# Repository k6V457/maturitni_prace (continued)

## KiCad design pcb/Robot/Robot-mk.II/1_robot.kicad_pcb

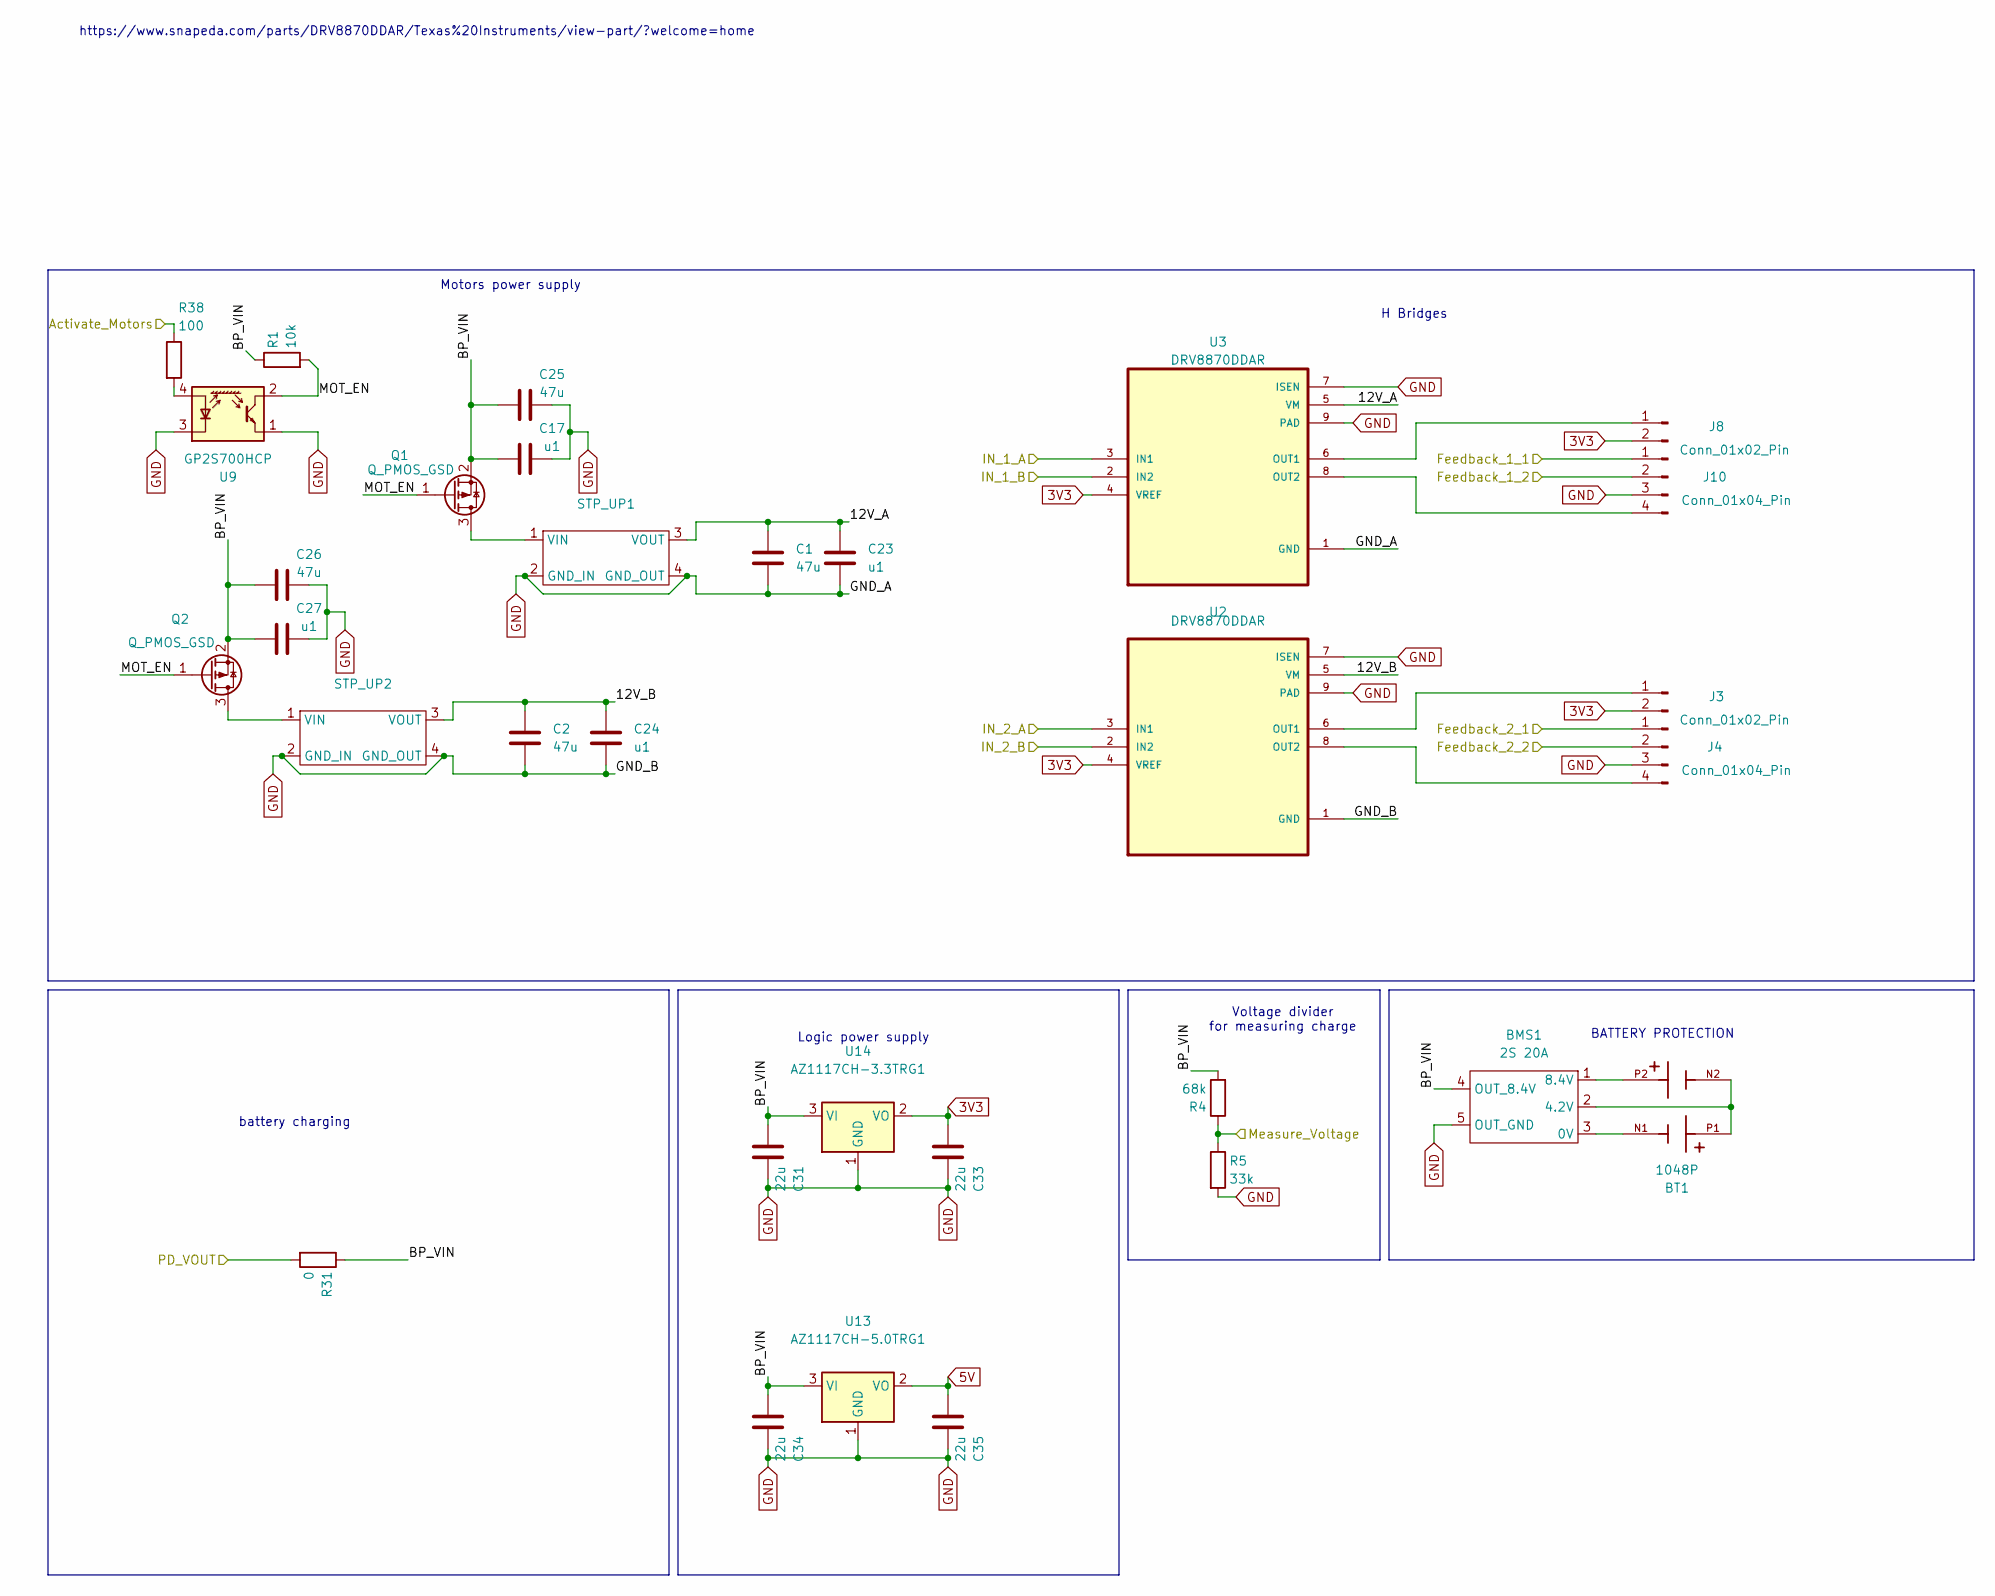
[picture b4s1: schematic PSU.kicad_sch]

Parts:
BMS1: 2S 20A; BMS
BT1: 1048P; BAT_1048P; PARTREV A
C1, C2, C25, C26: 47u; C_0805_2012Metric_Pad1.18x1.45mm_HandSolder
C17, C23, C24, C27: u1; C_0805_2012Metric_Pad1.18x1.45mm_HandSolder
C31, C33, C34, C35: 22u; C_0805_2012Metric_Pad1.18x1.45mm_HandSolder
J3, J8: Conn_01x02_Pin; JST_EH_B2B-EH-A_1x02_P2.50mm_Vertical
J4, J10: Conn_01x04_Pin; JST_EH_B4B-EH-A_1x04_P2.50mm_Vertical
Q1, Q2: Q_PMOS_GSD; SOT-23
R1: 10k; R_0805_2012Metric_Pad1.20x1.40mm_HandSolder
R4: 68k; R_0805_2012Metric_Pad1.20x1.40mm_HandSolder
R5: 33k; R_0805_2012Metric_Pad1.20x1.40mm_HandSolder
R31: 0; R_0805_2012Metric_Pad1.20x1.40mm_HandSolder
R38: 100; R_0805_2012Metric_Pad1.20x1.40mm_HandSolder
STP_UP1, STP_UP2: STP_UP
U2, U3: DRV8870DDAR; VREG_LM5017MR_NOPB
U9: GP2S700HCP; SSOP-4_4.4x2.6mm_P1.27mm
U13: AZ1117CH-5.0TRG1; SOT-223-3_TabPin2
U14: AZ1117CH-3.3TRG1; SOT-223-3_TabPin2

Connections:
3V3: C33.2, J3.2, J8.2, U2.4 (VREF), U3.4 (VREF), U14.2 (VO); also elsewhere on the board
5V: C35.2, U13.2 (VO)
/ESP32/IO1: R4.1, R5.1; also elsewhere on the board
/ESP32/IO4: J4.2; also elsewhere on the board
/ESP32/IO5: J4.1; also elsewhere on the board
/ESP32/IO6: U2.3 (IN1); also elsewhere on the board
/ESP32/IO7: U2.2 (IN2); also elsewhere on the board
/ESP32/IO14: R38.1; also elsewhere on the board
/ESP32/IO15: J10.2; also elsewhere on the board
/ESP32/IO16: J10.1; also elsewhere on the board
/ESP32/IO17: U3.3 (IN1); also elsewhere on the board
/ESP32/IO18: U3.2 (IN2); also elsewhere on the board
/Input/PD_VOUT: R31.2; also elsewhere on the board
/PSU/12V_A: C1.1, C23.1, STP_UP1.3 (VOUT), U3.5 (VM)
/PSU/12V_B: C2.1, C24.1, STP_UP2.3 (VOUT), U2.5 (VM)
/PSU/BP_VIN: BMS1.4 (OUT_8.4V), C17.2, C25.2, C26.2, C27.2, C31.2, C34.2, Q1.2 (S), Q2.2 (S), R1.1, R4.2, R31.1, U13.3 (VI), U14.3 (VI)
/PSU/MOT_EN: Q1.1 (G), Q2.1 (G), R1.2, U9.2
GND: BMS1.5 (OUT_GND), C1.2, C2.2, C17.1, C23.2, C24.2, C25.1, C26.1, C27.1, C31.1, C33.1, C34.1, C35.1, J4.3, J10.3, R5.2, STP_UP1.2 (GND_IN), STP_UP1.4 (GND_OUT), STP_UP2.2 (GND_IN), STP_UP2.4 (GND_OUT), U2.1 (GND), U2.7 (ISEN), U2.9 (PAD), U3.1 (GND), U3.7 (ISEN), U3.9 (PAD), U9.1, U9.3 (K), U13.1 (GND), U14.1 (GND); also elsewhere on the board
unnamed: BMS1.3 (0V), BT1.N1
unnamed: BMS1.2 (4.2V), BT1.N2, BT1.P1
unnamed: BMS1.1 (8.4V), BT1.P2
unnamed: J3.1, U2.6 (OUT1)
unnamed: J4.4, U2.8 (OUT2)
unnamed: J8.1, U3.6 (OUT1)
unnamed: J10.4, U3.8 (OUT2)
unnamed: Q1.3 (D), STP_UP1.1 (VIN)
unnamed: Q2.3 (D), STP_UP2.1 (VIN)
unnamed: R38.2, U9.4 (A)

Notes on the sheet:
battery charging
BATTERY PROTECTION
Logic power supply
H Bridges
Motors power supply
Voltage divider for measuring charge
https://www.snapeda.com/parts/DRV8870DDAR/Texas%20Instruments/view-part/?welcome=home

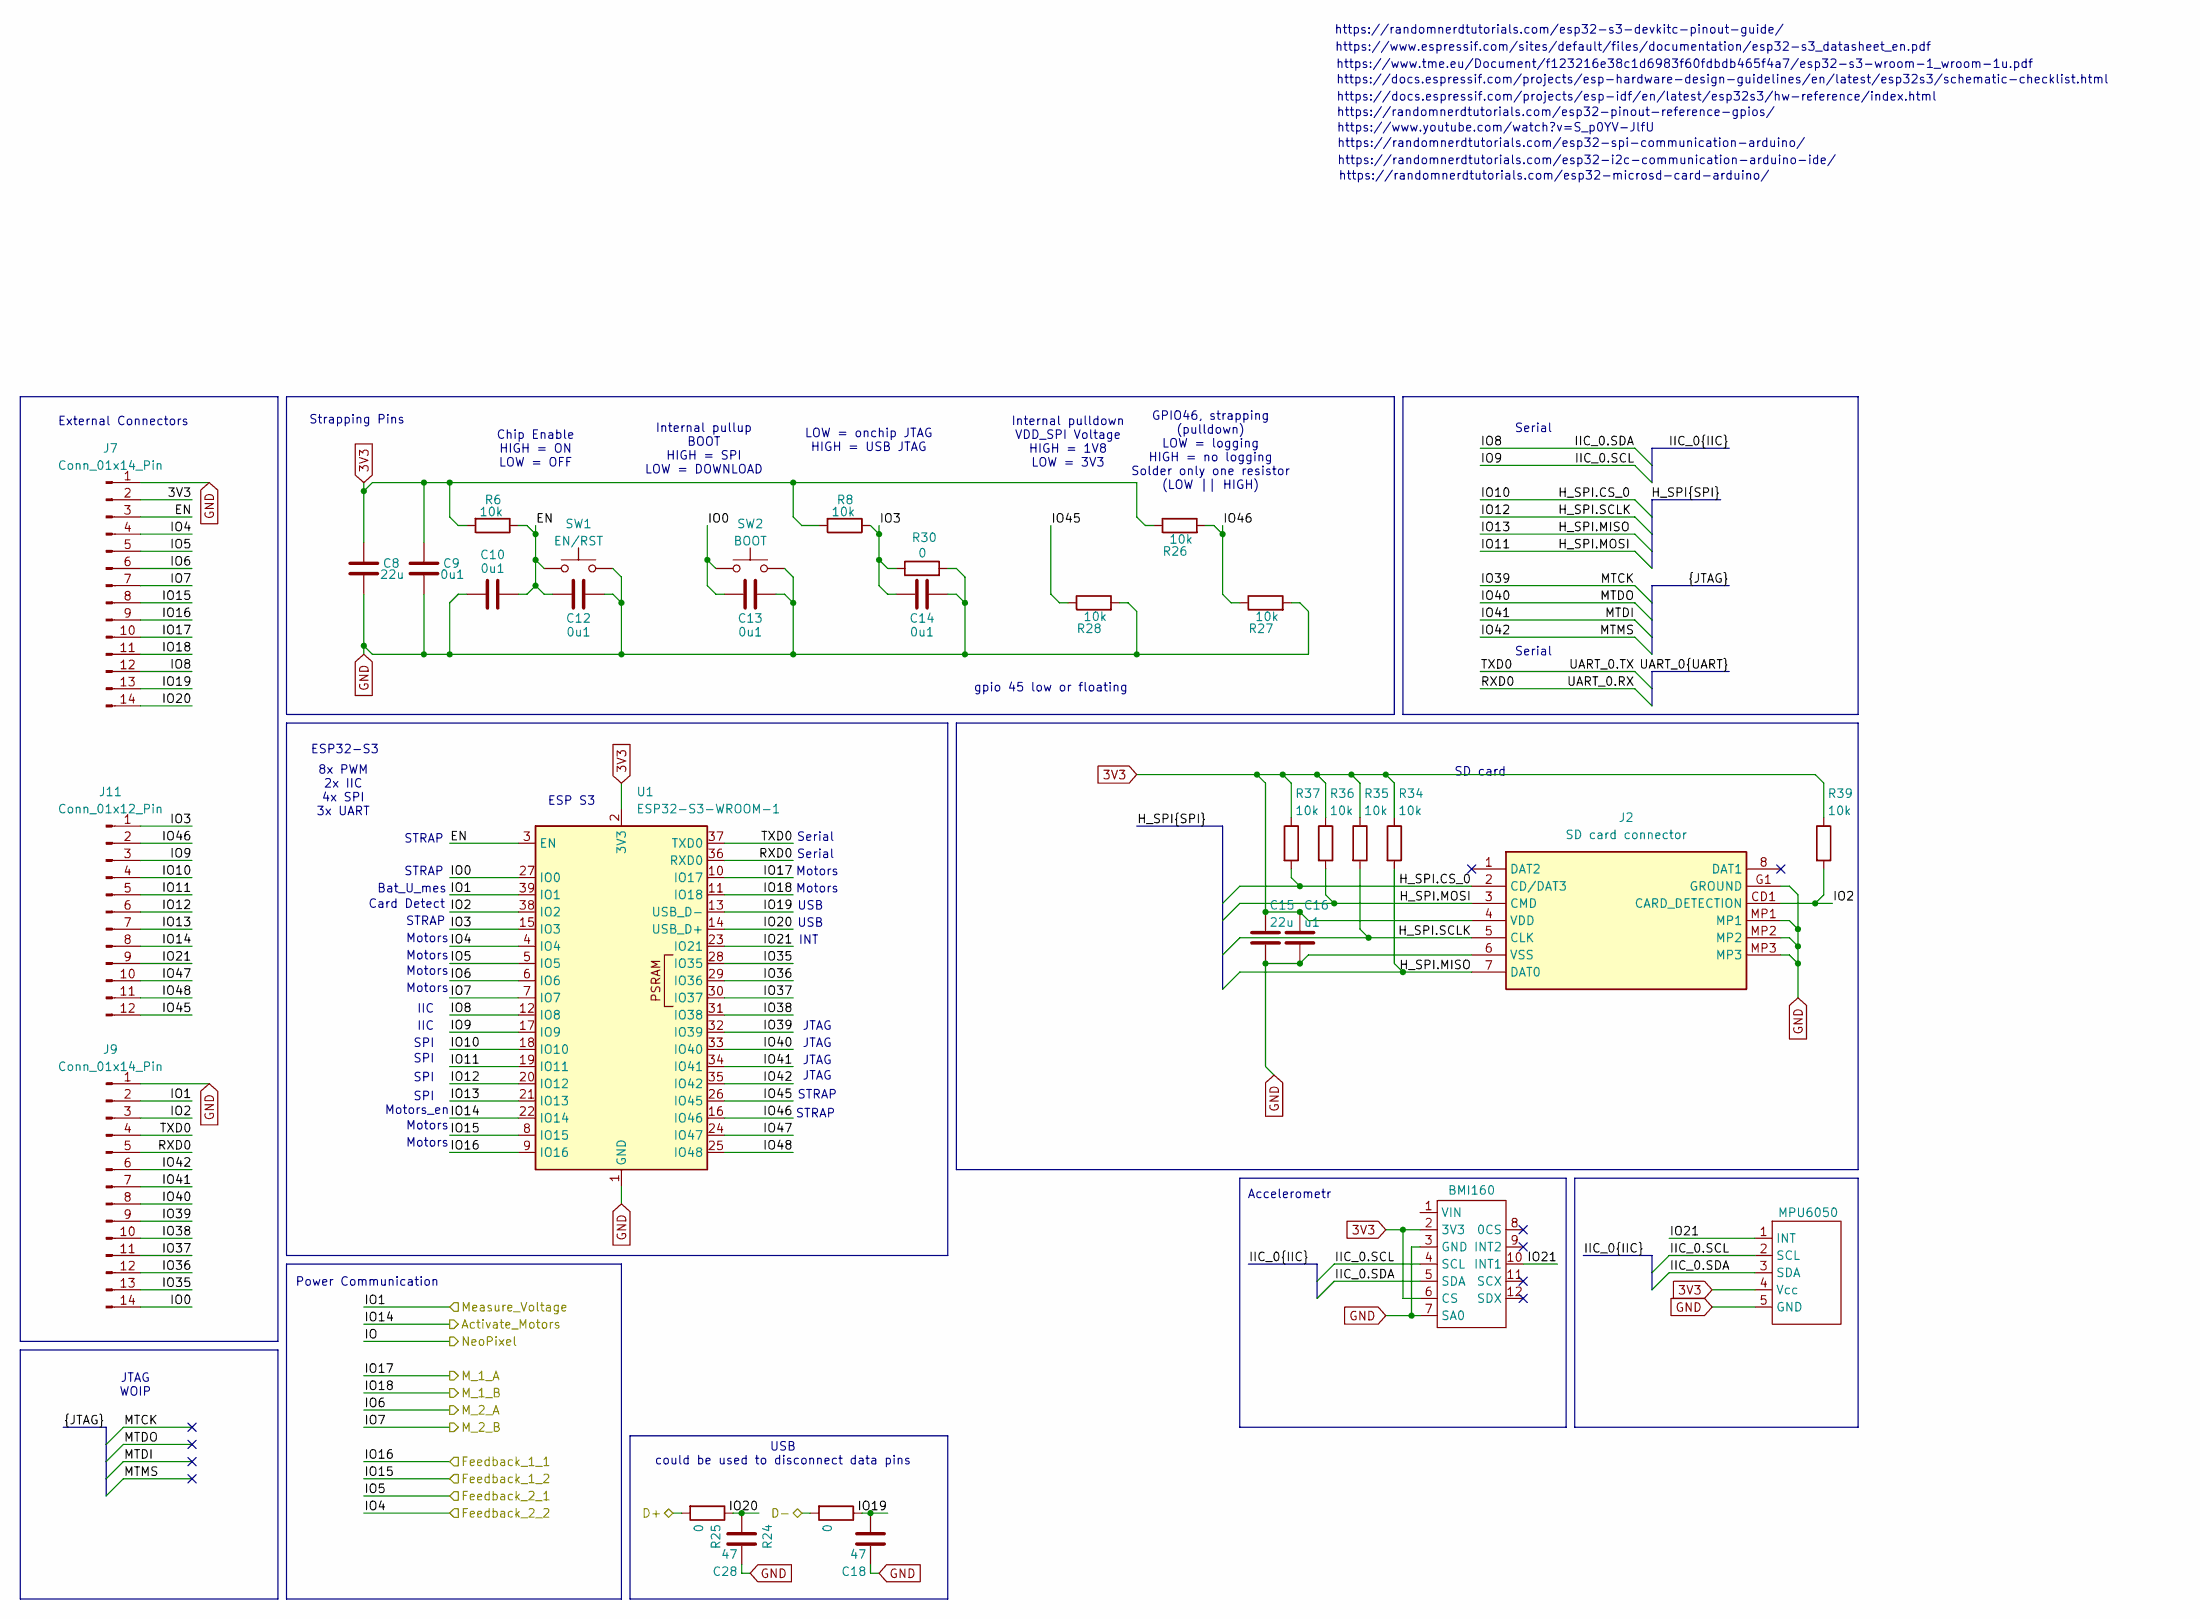
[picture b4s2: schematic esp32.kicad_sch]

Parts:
BMI160: BMI160
C8, C15: 22u; C_0805_2012Metric_Pad1.18x1.45mm_HandSolder
C9, C10, C12, C13, C14: 0u1; C_0805_2012Metric_Pad1.18x1.45mm_HandSolder
C16: u1; C_0805_2012Metric_Pad1.18x1.45mm_HandSolder
C18, C28: 47; C_0805_2012Metric_Pad1.18x1.45mm_HandSolder
J2: SD card connector; Manufacturer_Part_Number 112J-TDAR-R01
J7, J9: Conn_01x14_Pin; PinHeader_2x07_P2.54mm_Vertical
J11: Conn_01x12_Pin; PinHeader_2x06_P2.54mm_Vertical
MPU6050: BMU6050
R6, R8, R26, R27, R28, R34, R35, R36, R37, R39: 10k; R_0805_2012Metric_Pad1.20x1.40mm_HandSolder
R24, R25, R30: 0; R_0805_2012Metric_Pad1.20x1.40mm_HandSolder
SW1: EN/RST; SW_TL3305AF160QG
SW2: BOOT; SW_TL3305AF160QG
U1: ESP32-S3-WROOM-1

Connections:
3V3: BMI160.2 (3V3), BMI160.6 (CS), C8.1, C9.1, C15.1, C16.1, J2.4 (VDD), J7.2, MPU6050.4 (Vcc), R6.2, R8.2, R26.1, R34.1, R35.1, R36.1, R37.1, R39.1, U1.2 (3V3); also elsewhere on the board
/ESP32/D+: R25.2; also elsewhere on the board
/ESP32/D-: R24.2; also elsewhere on the board
/ESP32/EN: C10.1, C12.2, J7.3, R6.1, SW1.1, U1.3 (EN)
/ESP32/H_SPI.CS_0: J2.2 (CD/DAT3), J11.4, R37.2, U1.18 (IO10)
/ESP32/H_SPI.MISO: J2.7 (DAT0), J11.7, R34.2, U1.21 (IO13)
/ESP32/H_SPI.MOSI: J2.3 (CMD), J11.5, R36.2, U1.19 (IO11)
/ESP32/H_SPI.SCLK: J2.5 (CLK), J11.6, R35.2, U1.20 (IO12)
/ESP32/IIC_0.SCL: BMI160.4 (SCL), J11.3, MPU6050.2 (SCL), U1.17 (IO9)
/ESP32/IIC_0.SDA: BMI160.5 (SDA), J7.12, MPU6050.3 (SDA), U1.12 (IO8)
/ESP32/IO0: C13.1, J9.14, SW2.2, U1.27 (IO0)
/ESP32/IO1: J9.2, U1.39 (IO1); also elsewhere on the board
/ESP32/IO2: J2.CD1 (CARD_DETECTION), J9.3, R39.2, U1.38 (IO2)
/ESP32/IO3: C14.1, J11.1, R8.1, R30.1, U1.15 (IO3)
/ESP32/IO4: J7.4, U1.4 (IO4); also elsewhere on the board
/ESP32/IO5: J7.5, U1.5 (IO5); also elsewhere on the board
/ESP32/IO6: J7.6, U1.6 (IO6); also elsewhere on the board
/ESP32/IO7: J7.7, U1.7 (IO7); also elsewhere on the board
/ESP32/IO14: J11.8, U1.22 (IO14); also elsewhere on the board
/ESP32/IO15: J7.8, U1.8 (IO15); also elsewhere on the board
/ESP32/IO16: J7.9, U1.9 (IO16); also elsewhere on the board
/ESP32/IO17: J7.10, U1.10 (IO17); also elsewhere on the board
/ESP32/IO18: J7.11, U1.11 (IO18); also elsewhere on the board
/ESP32/IO19: C18.2, J7.13, R24.1, U1.13 (USB_D-)
/ESP32/IO20: C28.2, J7.14, R25.1, U1.14 (USB_D+)
/ESP32/IO21: BMI160.10 (INT1), J11.9, MPU6050.1 (INT), U1.23 (IO21)
/ESP32/IO35: J9.13, U1.28 (IO35)
/ESP32/IO36: J9.12, U1.29 (IO36)
/ESP32/IO37: J9.11, U1.30 (IO37)
/ESP32/IO38: J9.10, U1.31 (IO38)
/ESP32/IO39: J9.9, U1.32 (IO39)
/ESP32/IO40: J9.8, U1.33 (IO40)
/ESP32/IO41: J9.7, U1.34 (IO41)
/ESP32/IO42: J9.6, U1.35 (IO42)
/ESP32/IO45: J11.12, R28.1, U1.26 (IO45)
/ESP32/IO46: J11.2, R26.2, R27.1, U1.16 (IO46)
/ESP32/IO47: J11.10, U1.24 (IO47)
/ESP32/IO48: J11.11, U1.25 (IO48)
/ESP32/UART_0.RX: J9.5, U1.36 (RXD0)
/ESP32/UART_0.TX: J9.4, U1.37 (TXD0)
GND: BMI160.3 (GND), BMI160.7 (SA0), C8.2, C9.2, C10.2, C12.1, C13.2, C14.2, C15.2, C16.2, C18.1, C28.1, J2.6 (VSS), J2.G1 (GROUND), J2.MP1, J2.MP2, J2.MP3, J7.1, J9.1, MPU6050.5 (GND), R27.2, R28.2, R30.2, SW1.2, SW2.1, U1.1 (GND), U1.40 (GND), U1.41 (GND); also elsewhere on the board

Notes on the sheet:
JTAG
https://randomnerdtutorials.com/esp32-microsd-card-arduino/
Motors
Internal pulldown VDD_SPI Voltage HIGH = 1V8 LOW = 3V3
gpio 45 low or floating
SPI
Serial
https://randomnerdtutorials.com/esp32-i2c-communication-arduino-ide/
SD card
https://www.espressif.com/sites/default/files/documentation/esp32-s3_datasheet_en.pdf
STRAP
IIC
Internal pullup BOOT HIGH = SPI LOW = DOWNLOAD
https://www.youtube.com/watch?v=S_p0YV-JlfU
Strapping Pins
Motors_en
USB could be used to disconnect data pins
INT
8x PWM 2x IIC 4x SPI 3x UART
https://www.tme.eu/Document/f123216e38c1d6983f60fdbdb465f4a7/esp32-s3-wroom-1_wroom-1u.pdf
https://docs.espressif.com/projects/esp-idf/en/latest/esp32s3/hw-reference/index.html
Accelerometr
ESP S3
USB
https://randomnerdtutorials.com/esp32-pinout-reference-gpios/
JTAG
Card Detect
JTAG WOIP
Chip Enable HIGH = ON LOW = OFF
ESP32-S3
https://randomnerdtutorials.com/esp32-spi-communication-arduino/
https://randomnerdtutorials.com/esp32-s3-devkitc-pinout-guide/
Serial
GPIO46, strapping (pulldown) LOW = logging HIGH = no logging Solder only one resistor (LOW || HIGH)
https://docs.espressif.com/projects/esp-hardware-design-guidelines/en/latest/esp32s3/schematic-checklist.html
External Connectors
SPI
Power Communication
LOW = onchip JTAG HIGH = USB JTAG
Bat_U_mes

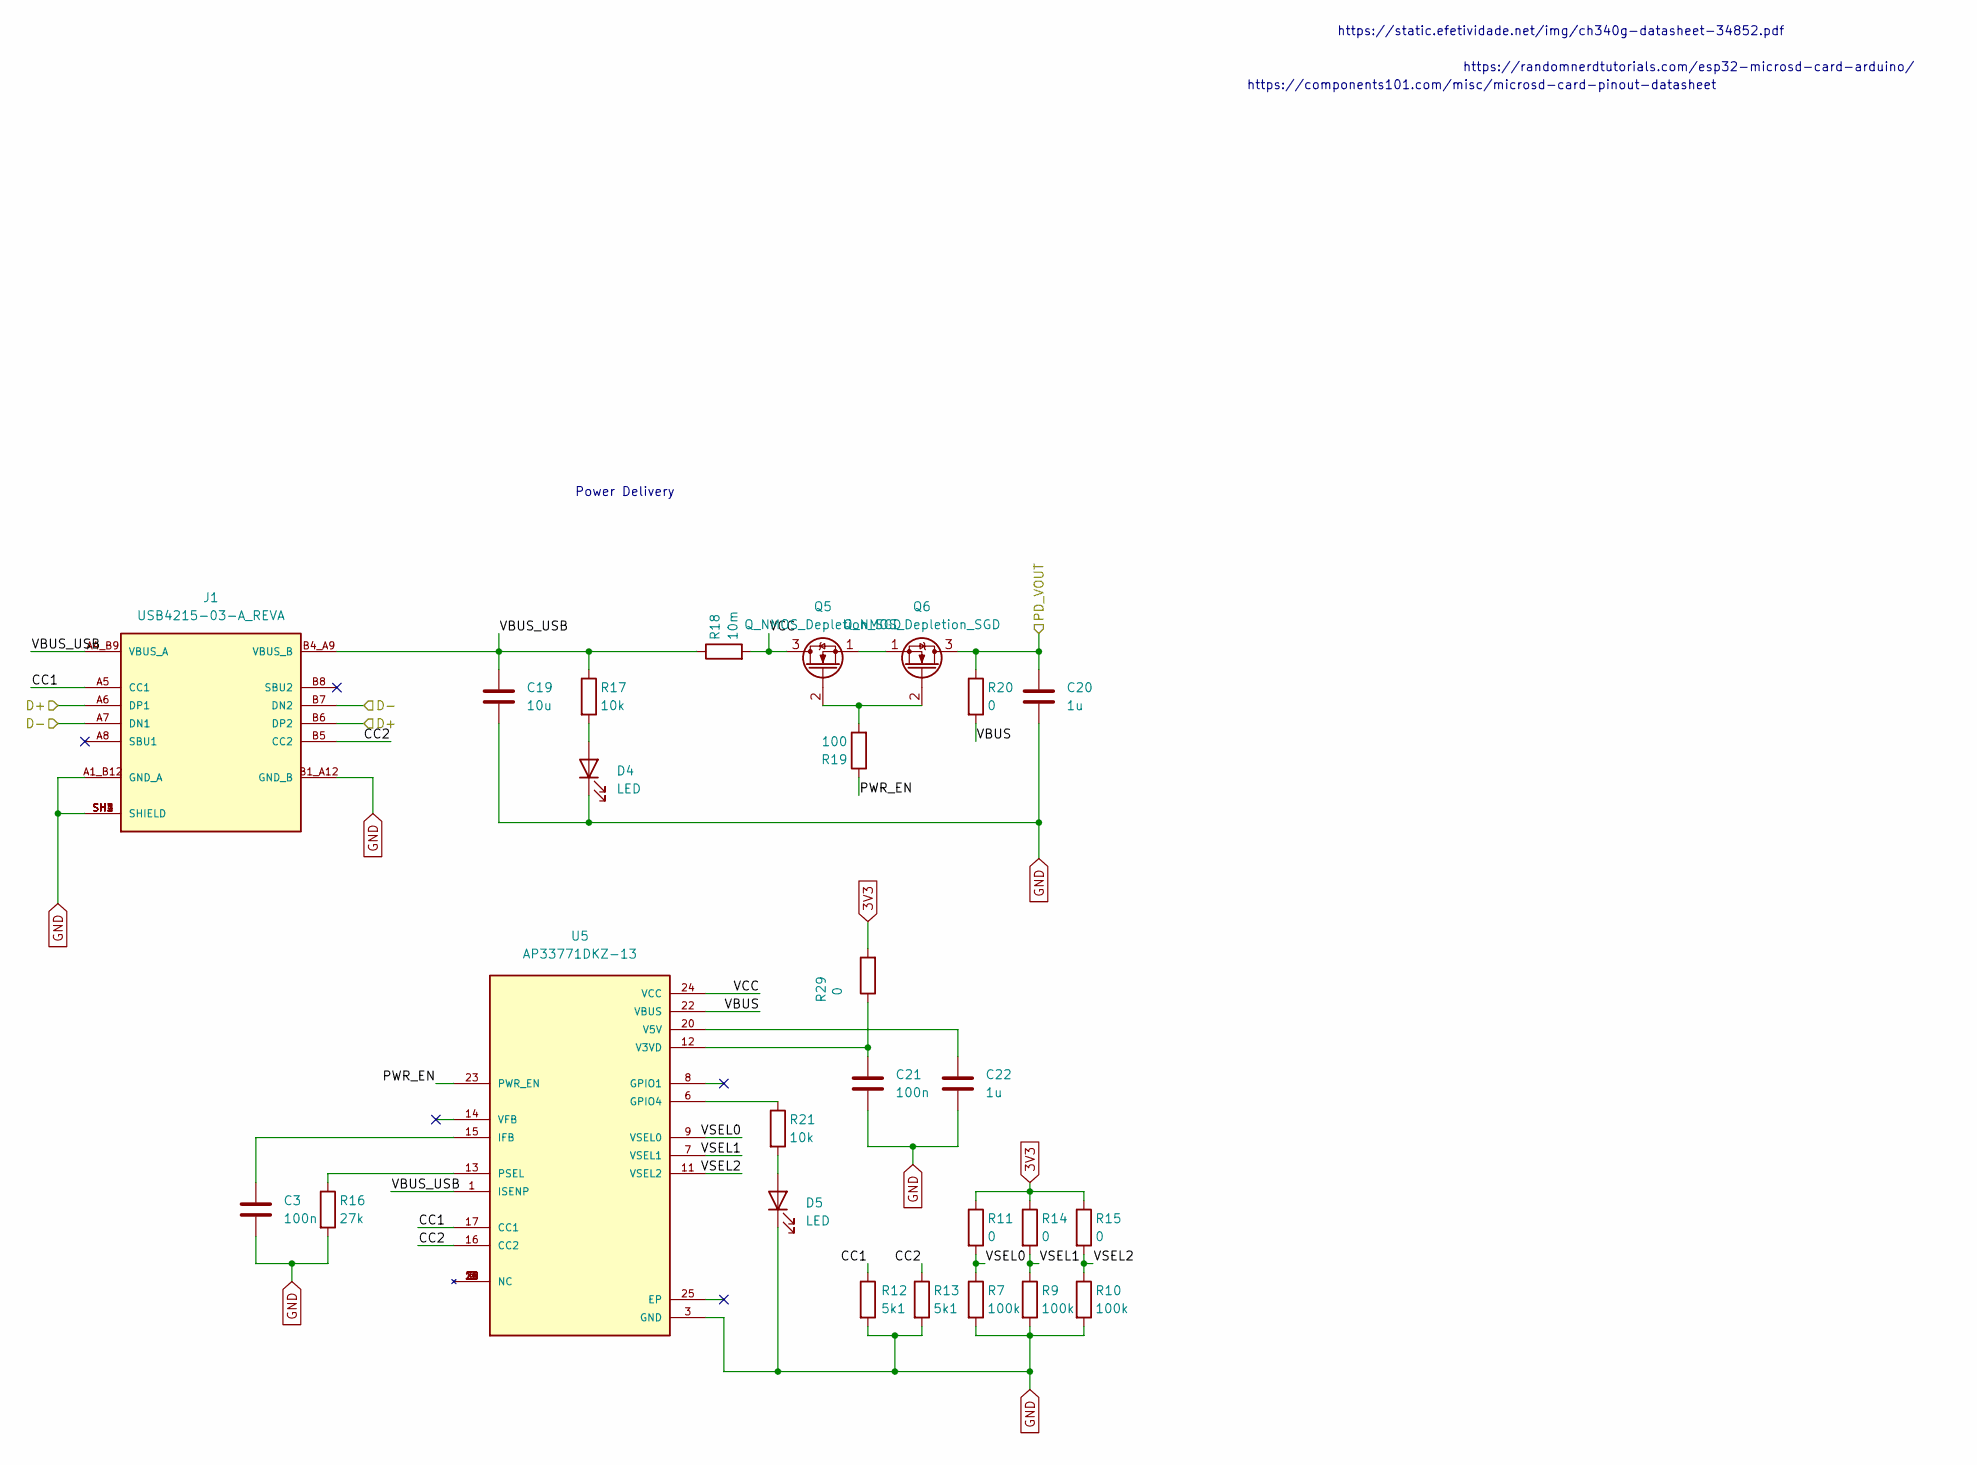
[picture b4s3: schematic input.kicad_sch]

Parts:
C3, C21: 100n; C_0805_2012Metric_Pad1.18x1.45mm_HandSolder
C19: 10u; C_0805_2012Metric_Pad1.18x1.45mm_HandSolder
C20, C22: 1u; C_0805_2012Metric_Pad1.18x1.45mm_HandSolder
D4, D5: LED; LED_0805_2012Metric_Pad1.15x1.40mm_HandSolder
J1: USB4215-03-A_REVA; GCT_USB4215-03-A_REVA; PARTREV A
Q5, Q6: Q_NMOS_Depletion_SGD; SOT-23
R7, R9, R10: 100k; R_0805_2012Metric_Pad1.20x1.40mm_HandSolder
R11, R14, R15, R20, R29: 0; R_0805_2012Metric_Pad1.20x1.40mm_HandSolder
R12, R13: 5k1; R_0805_2012Metric_Pad1.20x1.40mm_HandSolder
R16: 27k; R_0805_2012Metric_Pad1.20x1.40mm_HandSolder
R17, R21: 10k; R_0805_2012Metric_Pad1.20x1.40mm_HandSolder
R18: 10m; R_0805_2012Metric_Pad1.20x1.40mm_HandSolder
R19: 100; R_0805_2012Metric_Pad1.20x1.40mm_HandSolder
U5: AP33771DKZ-13; IC_AP33771DKZ-13; PARTREV 5-2; DigiKey_Part_Number 31-AP33771DKZ-13TR-ND

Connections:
3V3: R11.1, R14.1, R15.1, R29.2; also elsewhere on the board
/ESP32/D+: J1.A6 (DP1), J1.B6 (DP2); also elsewhere on the board
/ESP32/D-: J1.A7 (DN1), J1.B7 (DN2); also elsewhere on the board
/Input/CC1: J1.A5 (CC1), R12.1, U5.17 (CC1)
/Input/CC2: J1.B5 (CC2), R13.1, U5.16 (CC2)
/Input/PD_VOUT: C20.1, Q6.3 (D), R20.1; also elsewhere on the board
/Input/PWR_EN: R19.1, U5.23 (PWR_EN)
/Input/VBUS: R20.2, U5.22 (VBUS)
/Input/VBUS_USB: C19.1, J1.A4_B9 (VBUS_A), J1.B4_A9 (VBUS_B), R17.1, R18.1, U5.1 (ISENP)
/Input/VCC: Q5.3 (D), R18.2, U5.24 (VCC)
/Input/VSEL0: R7.1, R11.2, U5.9 (VSEL0)
/Input/VSEL1: R9.1, R14.2, U5.7 (VSEL1)
/Input/VSEL2: R10.1, R15.2, U5.11 (VSEL2)
GND: C3.2, C19.2, C20.2, C21.2, C22.2, D4.1 (K), D5.1 (K), J1.A1_B12 (GND_A), J1.B1_A12 (GND_B), J1.SH1 (SHIELD), J1.SH2 (SHIELD), J1.SH3 (SHIELD), J1.SH4 (SHIELD), R7.2, R9.2, R10.2, R12.2, R13.2, R16.2, U5.3 (GND); also elsewhere on the board
unnamed: D4.2 (A), R17.2
unnamed: D5.2 (A), R21.2
unnamed: Q5.2 (G), Q6.2 (G), R19.2
unnamed: Q5.1 (S), Q6.1 (S)
unnamed: R21.1, U5.6 (GPIO4)
unnamed: C3.1, U5.15 (IFB)
unnamed: R16.1, U5.13 (PSEL)
unnamed: C21.1, R29.1, U5.12 (V3VD)
unnamed: C22.1, U5.20 (V5V)

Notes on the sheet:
Power Delivery
https://components101.com/misc/microsd-card-pinout-datasheet
https://static.efetividade.net/img/ch340g-datasheet-34852.pdf
https://randomnerdtutorials.com/esp32-microsd-card-arduino/

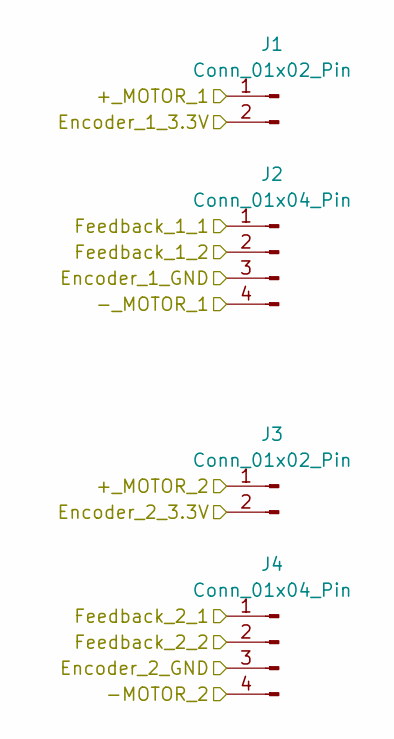
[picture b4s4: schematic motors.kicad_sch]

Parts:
J1, J3: Conn_01x02_Pin; JST_EH_B6B-EH-A_1x06_P2.50mm_Vertical
J2, J4: Conn_01x04_Pin

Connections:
3V3: J2.4 (VDD), J3.2; also elsewhere on the board
/ESP32/H_SPI.CS_0: J2.2 (CD/DAT3); also elsewhere on the board
/ESP32/H_SPI.MOSI: J2.3 (CMD); also elsewhere on the board
/ESP32/IO4: J4.2; also elsewhere on the board
/ESP32/IO5: J4.1; also elsewhere on the board
GND: J4.3; also elsewhere on the board
unnamed 61: J3.1; also elsewhere on the board
unnamed 62: J4.4; also elsewhere on the board

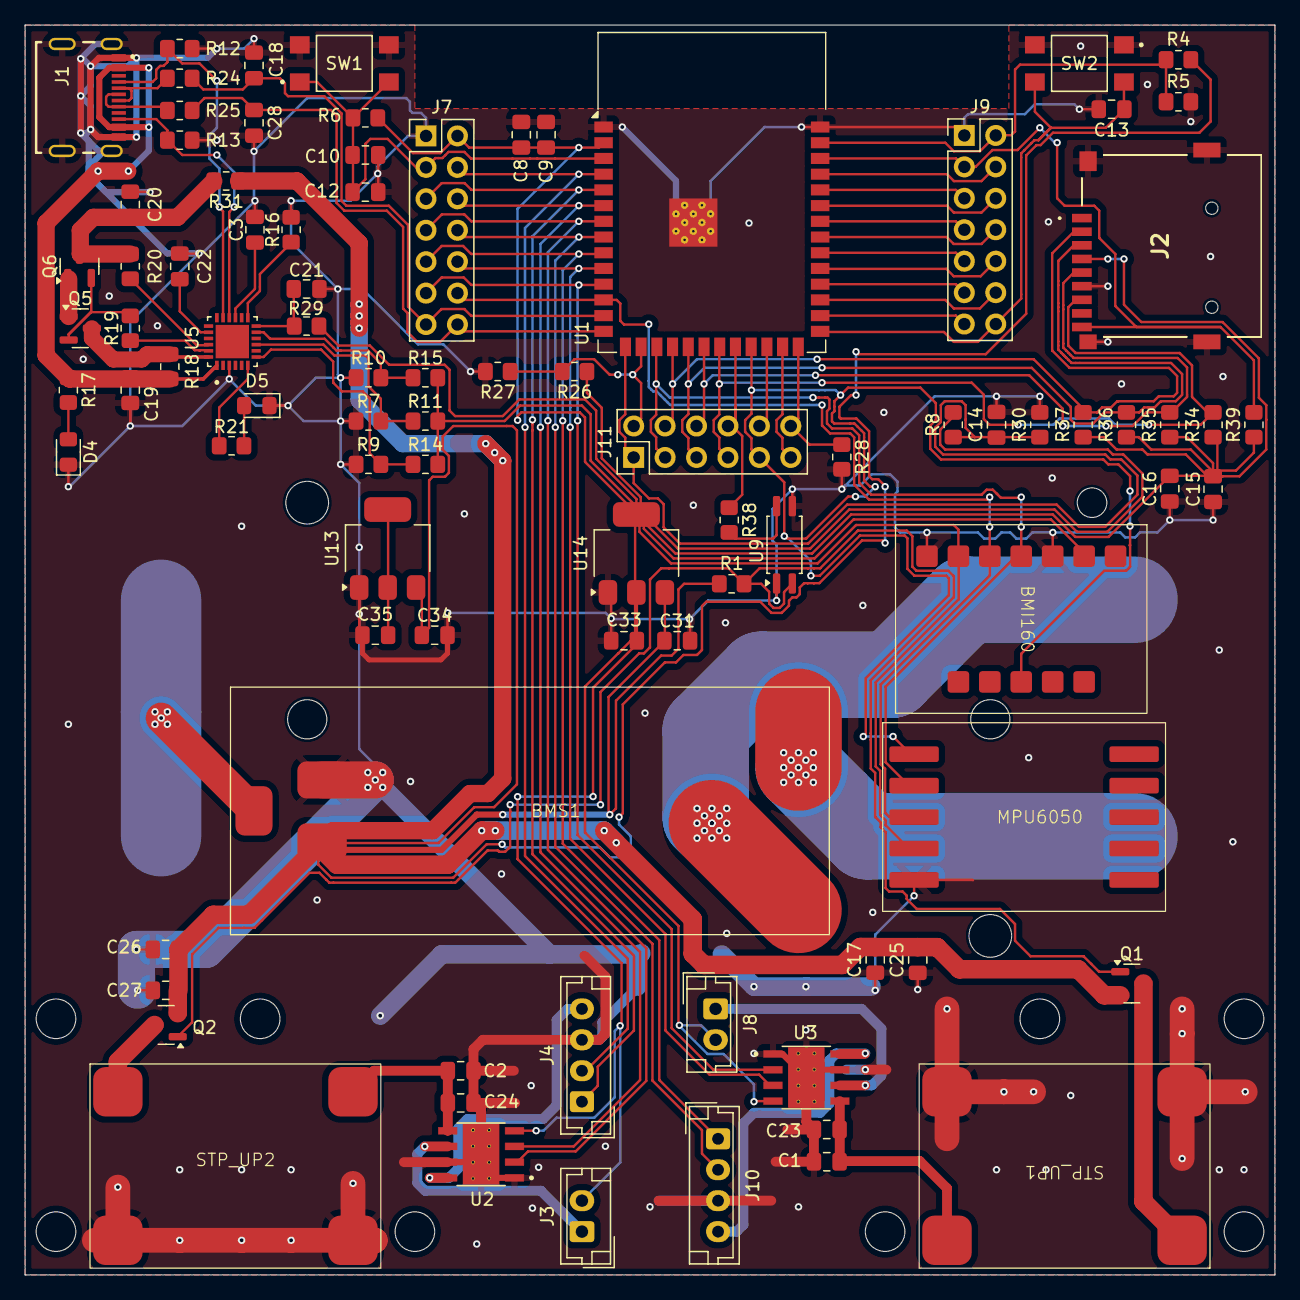
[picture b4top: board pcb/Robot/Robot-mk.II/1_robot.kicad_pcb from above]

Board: 2 copper layers, 101.0 x 101.0 mm, 90 parts (1 on the bottom side), 75 nets.

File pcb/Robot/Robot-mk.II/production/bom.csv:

Designator,Footprint,Quantity,Value,LCSC Part #
BMI160,BMI160,1,~,
BMS1,BMS,1,2S 20A,
BT1,BAT_1048P,1,1048P,
"C1, C2, C25, C26",0805,4,47u,
"C10, C12, C13, C14, C9",0805,5,0u1,
"C15, C31, C33, C34, C35, C8",0805,6,22u,
"C16, C17, C23, C24, C27",0805,5,u1,
"C18, C28",0805,2,47,
C19,0805,1,10u,
"C20, C22",0805,2,1u,
"C21, C3",0805,2,100n,
"D4, D5",0805,2,LED,
J1,GCT_USB4215-03-A_REVA,1,USB4215-03-A_REVA,
"J10, J4",JST_EH_B4B-EH-A_1x04_P2.50mm_Vertical,2,Conn_01x04_Pin,
J11,PinHeader_2x06_P2.54mm_Vertical,1,Conn_01x12_Pin,
J2,SD card connector,1,SD card connector,
"J3, J8",JST_EH_B2B-EH-A_1x02_P2.50mm_Vertical,2,Conn_01x02_Pin,
"J7, J9",PinHeader_2x07_P2.54mm_Vertical,2,Conn_01x14_Pin,
MPU6050,BMU6050,1,~,
"Q1, Q2",SOT-23,2,Q_PMOS_GSD,
"Q5, Q6",SOT-23,2,Q_NMOS_Depletion_SGD,
"R1, R17, R21, R26, R27, R28, R34, R35, R36, R37, R39, R6, R8",0805,13,10k,
"R10, R7, R9",0805,3,100k,
"R11, R14, R15, R20, R24, R25, R29, R30, R31",0805,9,0,
"R12, R13",0805,2,5k1,
R16,0805,1,27k,
R18,0805,1,10m,
"R19, R38",0805,2,100,
R4,0805,1,68k,
R5,0805,1,33k,
"STP_UP1, STP_UP2",STP_UP,2,~,
SW1,SW_TL3305AF160QG,1,EN/RST,
SW2,SW_TL3305AF160QG,1,BOOT,
U1,ESP32-S3-WROOM-1,1,ESP32-S3-WROOM-1,
U13,SOT-223-3_TabPin2,1,AZ1117CH-5.0TRG1,
U14,SOT-223-3_TabPin2,1,AZ1117CH-3.3TRG1,
"U2, U3",VREG_LM5017MR_NOPB,2,DRV8870DDAR,
U5,IC_AP33771DKZ-13,1,AP33771DKZ-13,
U9,SSOP-4_4.4x2.6mm_P1.27mm,1,GP2S700HCP,

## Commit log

2024-09-25 It'd be rather nice to have backup
2024-09-25 added license
2024-11-13 Added "Práce_Obsidian"
2025-01-21 Create LICENSE
2025-01-21 Create README.md
    created thesis todo list
2025-01-30 30.1.2025 no big changes, going to get latex runing
2025-02-18 nastavení šablony LATEX
2025-03-15 migrating to new template TEX
2025-03-17 template set up
2025-03-18 psani teoreticke casti
2025-03-20 Kompletace teoretické části a počátky části praktické
2025-03-20 Something went terribly wring
2025-03-20 working
2025-03-20 synced with previous branch
2025-03-21 90% (40 pages)
2025-03-23 finished work
2025-04-04 before cleanup
